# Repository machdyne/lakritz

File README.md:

# Lakritz Computer

Lakritz is an FPGA computer designed by Lone Dynamics Corporation.

This repo contains schematics, PCB layouts, pinouts, a 3D-printable case, example gateware and documentation.

Find more information on the [Lakritz product page](https://machdyne.com/product/lakritz-computer/).

## Programming Lakritz

Lakritz has a JTAG interface and ships with a [DFU bootloader](https://github.com/machdyne/tinydfu-bootloader) that allows the included flash [MMOD](https://machdyne.com/product/mmod) to be programmed over the USB-C port.

### DFU

The DFU bootloader is available for 5 seconds after power-on, issuing a DFU command during this period will stop the boot process until the DFU device is detached. If no command is received the boot process will continue and the user gateware will be loaded.

Install [dfu-util](http://dfu-util.sourceforge.net) (Debian/Ubuntu):

```
$ sudo apt install dfu-util
```

Update the user gateware on the flash MMOD:

```
$ sudo dfu-util -a 0 -D image.bit
```

Detach the DFU device and continue the boot process:

```
$ sudo dfu-util -a 0 -e
```

It is possible to update the bootloader itself using DFU but you shouldn't attempt this unless you have a JTAG programmer (or another method to program the MMOD) available, in case you need to restore the bootloader.

### JTAG

These examples assume you're using a "USB Blaster" JTAG cable, see the header pinout below. You will need to have [openFPGALoader](https://github.com/trabucayre/openFPGALoader) installed.

Program the configuration SRAM:

```
openFPGALoader -c usb-blaster image.bit
```

Program the flash MMOD:

```
openFPGALoader -f -c usb-blaster images/bootloader/tinydfu_lakritz.bit
```

## Blinky 

Building the blinky example requires [Yosys](https://github.com/YosysHQ/yosys), [nextpnr-ecp5](https://github.com/YosysHQ/nextpnr) and [Project Trellis](https://github.com/YosysHQ/prjtrellis).

Assuming they are installed, you can simply type `make` to build the gateware, which will be written to output/lakritz.bit. You can then use [openFPGALoader](https://github.com/trabucayre/openFPGALoader) or dfu-util to write the gateware to the device.

## Linux

See the [Kakao Linux](https://github.com/machdyne/kakao) repo for the latest instructions.

### Prebuilt Images

Copy the files from the `images/linux` and `images/v0/25f` directory to the root directory of a FAT-formatted MicroSD card along with the files from the `images` directory in the [Kakao Linux](https://github.com/machdyne/kakao) repo.

Lakritz ships with LiteX gateware on the user gateware section of the MMOD that is compatible with these images. After several seconds the Linux penguin should appear on the screen (HDMI) followed by a login prompt.

### Building Linux

Please follow the setup instructions in the [linux-on-litex-vexriscv](https://github.com/litex-hub/linux-on-litex-vexriscv) repo and then:

1. Build the Linux-capable gateware:

```
$ cd linux-on-litex-vexriscv
$ ./make.py --board lakritz --uart-baudrate 115200 --dcache-size 64 --icache-size 64 --dcache-ways=1 --icache-ways=1 --dtlb-size 2 --itlb-size 2 --build
```

NOTE: This may fail, if so:

```
$ cd build/lakritz/gateware
```

Edit `lakritz.ys` and add the `-abc2` option as shown below:

```
synth_ecp5  -top lakritz -abc2
```

Now run:

```
$ bash build_lakritz.sh
```

2. Write the gateware to the MMOD using USB DFU:

```
$ sudo dfu-util -a 0 -D build/lakritz/gateware/lakritz.bit
```

3. Copy the device tree binary `build/lakritz/lakritz.dtb` to a FAT-formatted MicroSD card.

4. Build the Linux kernel and root filesystem:

See the [Kakao Linux](https://github.com/machdyne/kakao?tab=readme-ov-file#optional-building-kakao-linux) repo for instructions.

5. Copy the Image and rootfs.cpio files generated in the previous step to the boot partition of the MicroSD card, in addition to the following files:

6. Copy the OpenSBI binary (included in this repo as `lakritz/images/linux/opensbi.bin`) to the MicroSD card. Alternatively, you can build this binary by following [these instructions](https://github.com/litex-hub/linux-on-litex-vexriscv#-generating-the-opensbi-binary-optional).

7. Copy `lakritz/images/linux/boot.json` to the MicroSD card.

8. Power-cycle Lakritz. After Linux has finished booting you should see a login prompt on the HDMI display.

## JTAG Header

The 3.3V JTAG header can be used to program the FPGA SRAM as well as the MMOD flash memory. It can also be used to provide power (5V) to the board.

```
2 4 6
1 3 5
```

| Pin | Signal |
| --- | ------ |
| 1 | TCK |
| 2 | TDI |
| 3 | TDO |
| 4 | TMS |
| 5 | 5V0 |
| 6 | GND |

## Resources

 * [fpga-dac audio player](https://github.com/machdyne/fpga-dac)

## Board Revisions

| Revision | Notes |
| -------- | ----- |
| V0 | Initial version |

## License

The contents of this repo are released under the [Lone Dynamics Open License](LICENSE.md) with the following exceptions:

- The KiCad design files contain parts of the [kicad-pmod](https://github.com/mithro/kicad-pmod) library which is released under the [Apache License, Version 2.0](https://www.apache.org/licenses/LICENSE-2.0.html).

- The KiCad design files may contain symbols and footprints released under other licenses; please contact us if we've failed to give proper attribution.

Note: You can use these designs for commercial purposes but we ask that instead of producing exact clones, that you either replace our trademarks and logos with your own or add your own next to ours.

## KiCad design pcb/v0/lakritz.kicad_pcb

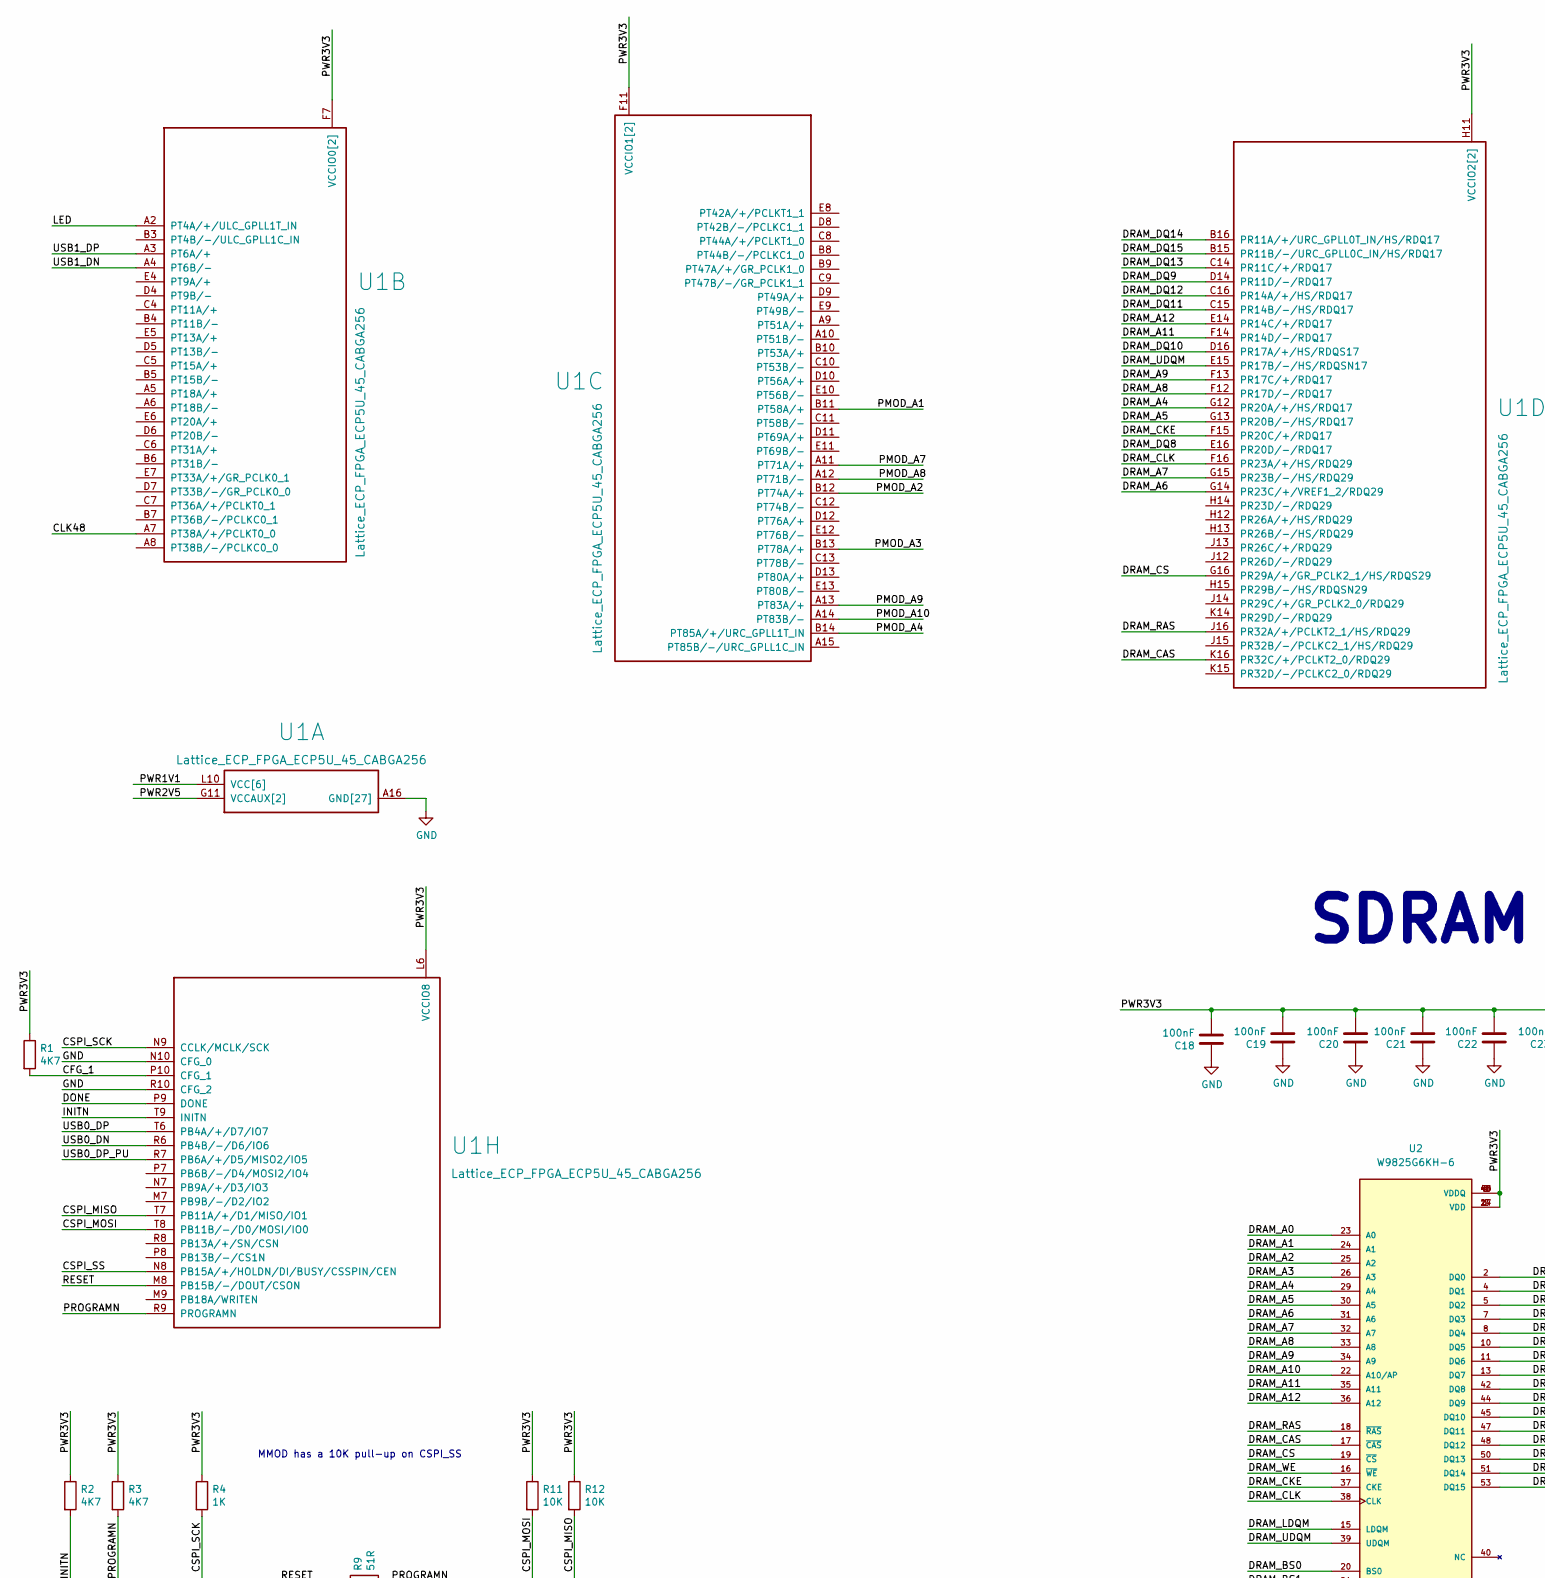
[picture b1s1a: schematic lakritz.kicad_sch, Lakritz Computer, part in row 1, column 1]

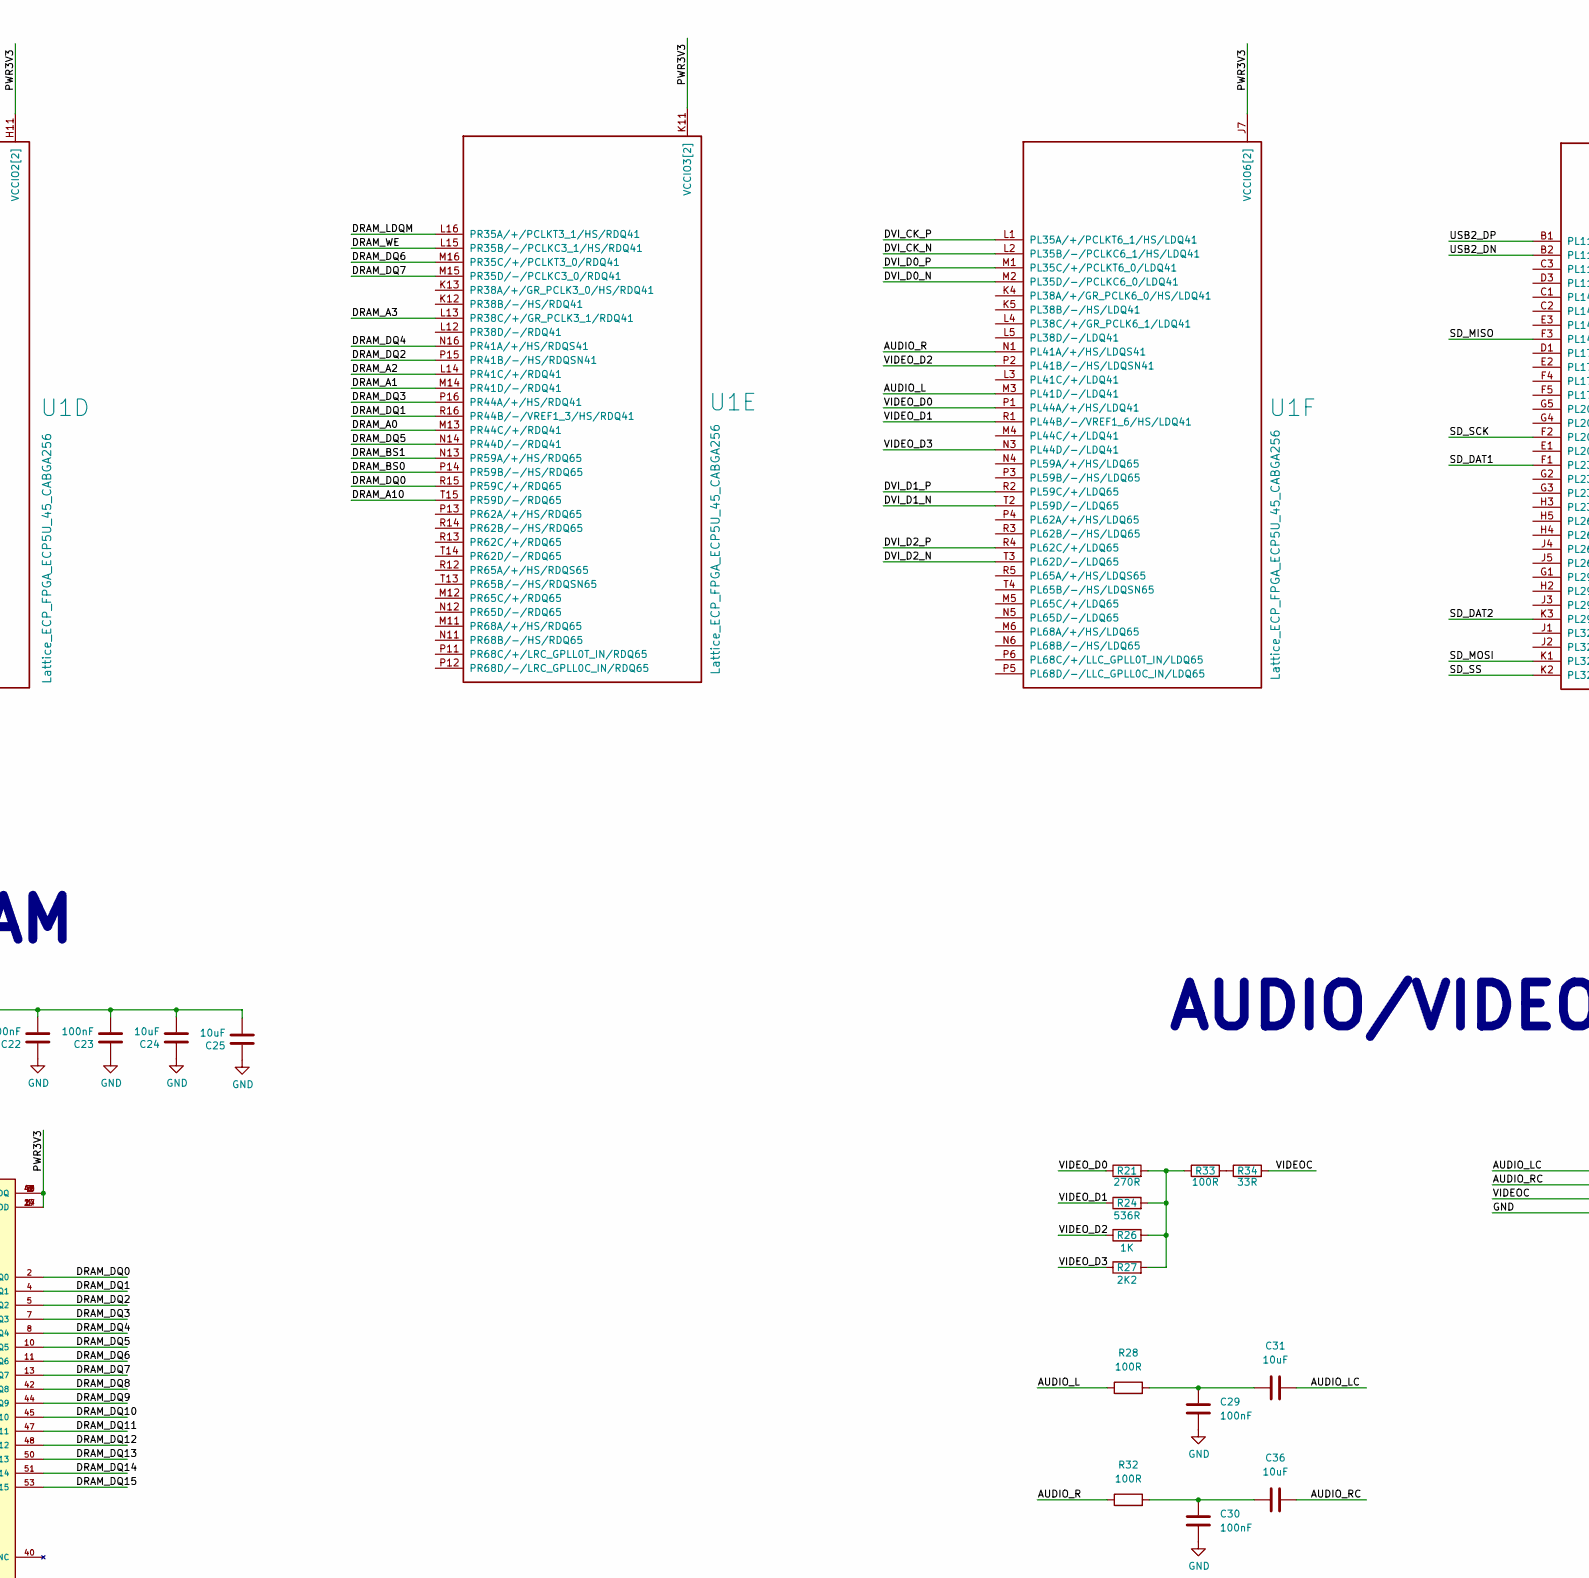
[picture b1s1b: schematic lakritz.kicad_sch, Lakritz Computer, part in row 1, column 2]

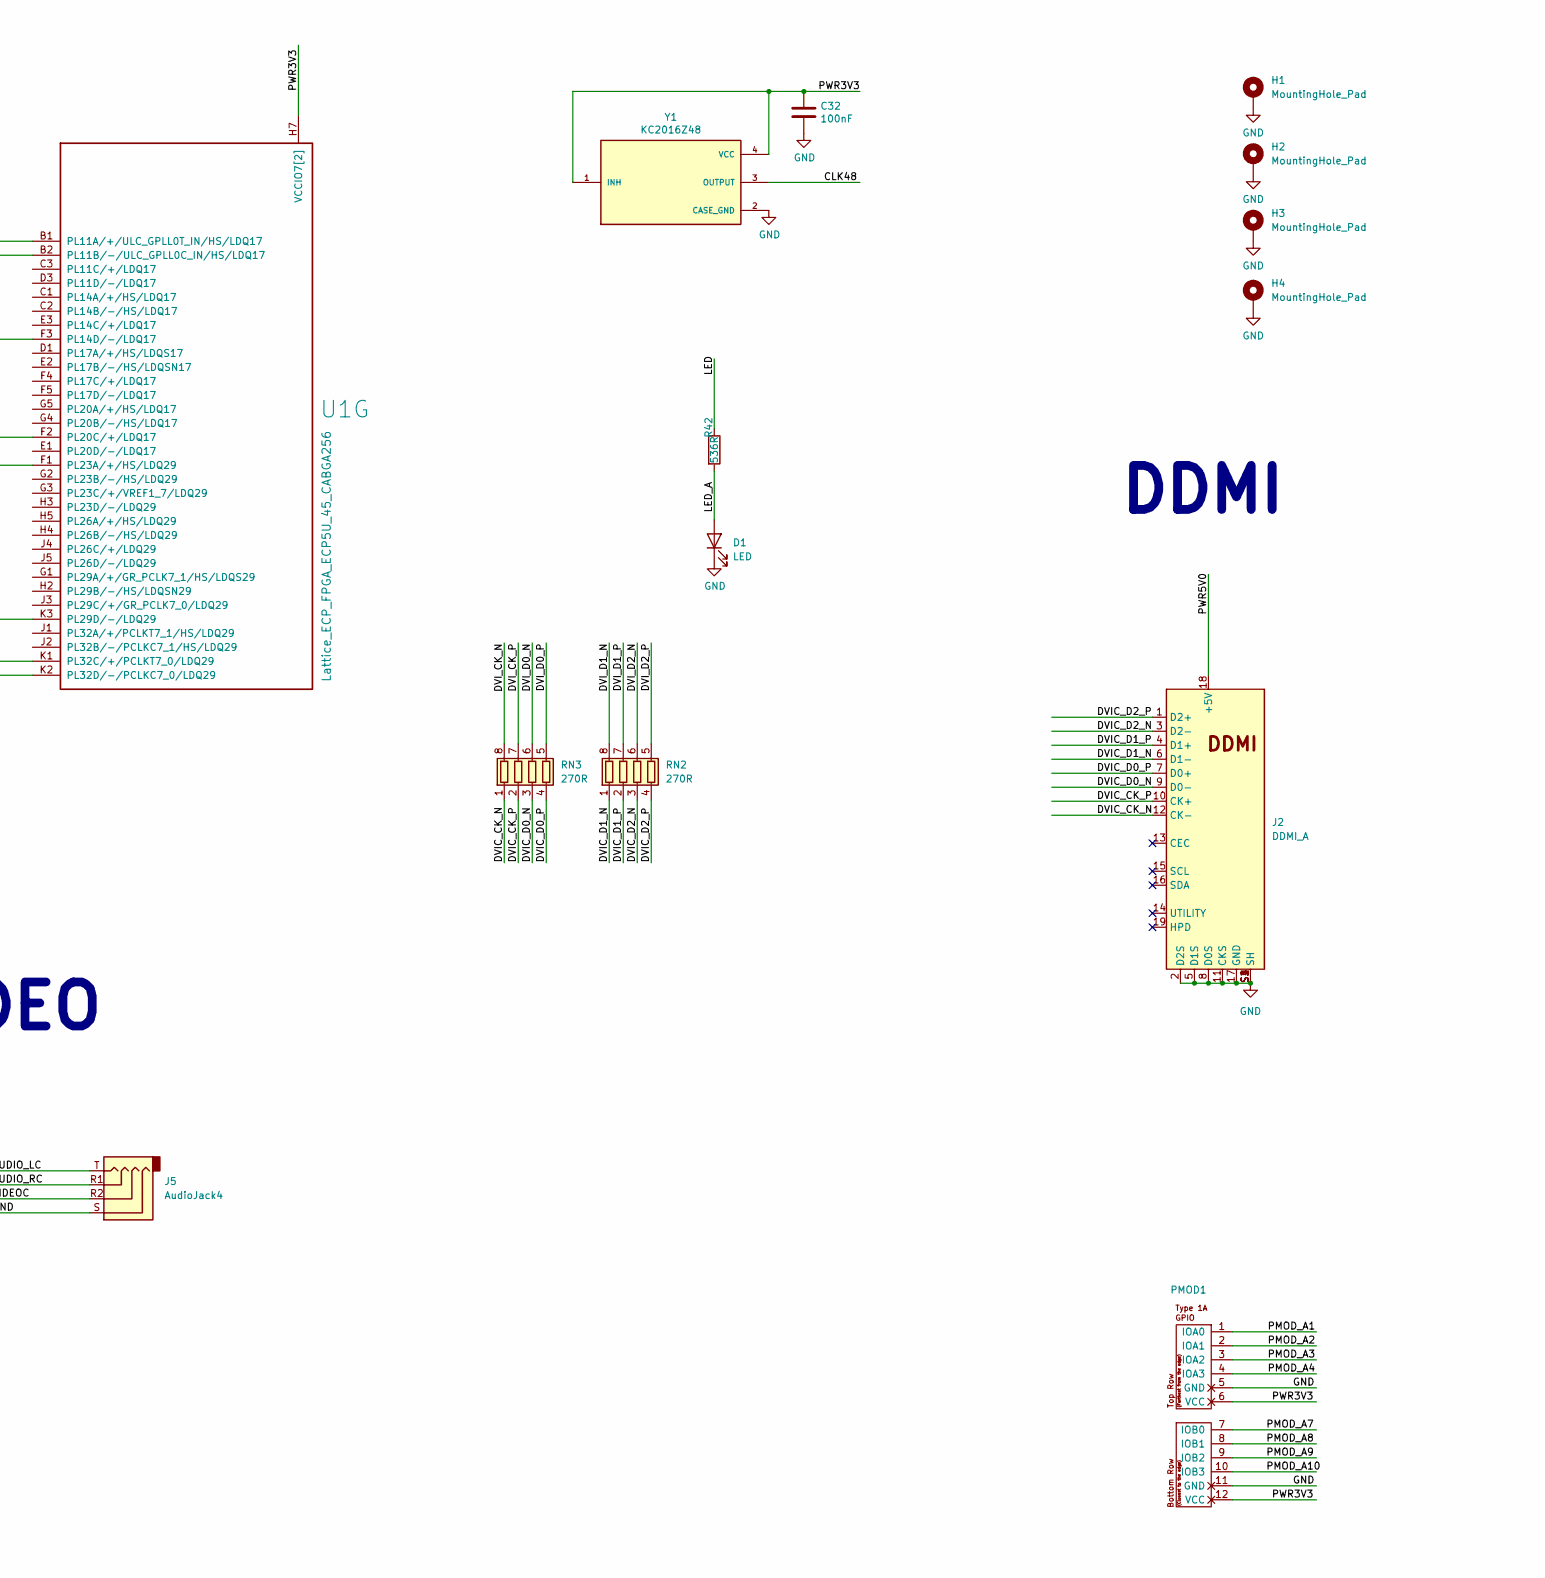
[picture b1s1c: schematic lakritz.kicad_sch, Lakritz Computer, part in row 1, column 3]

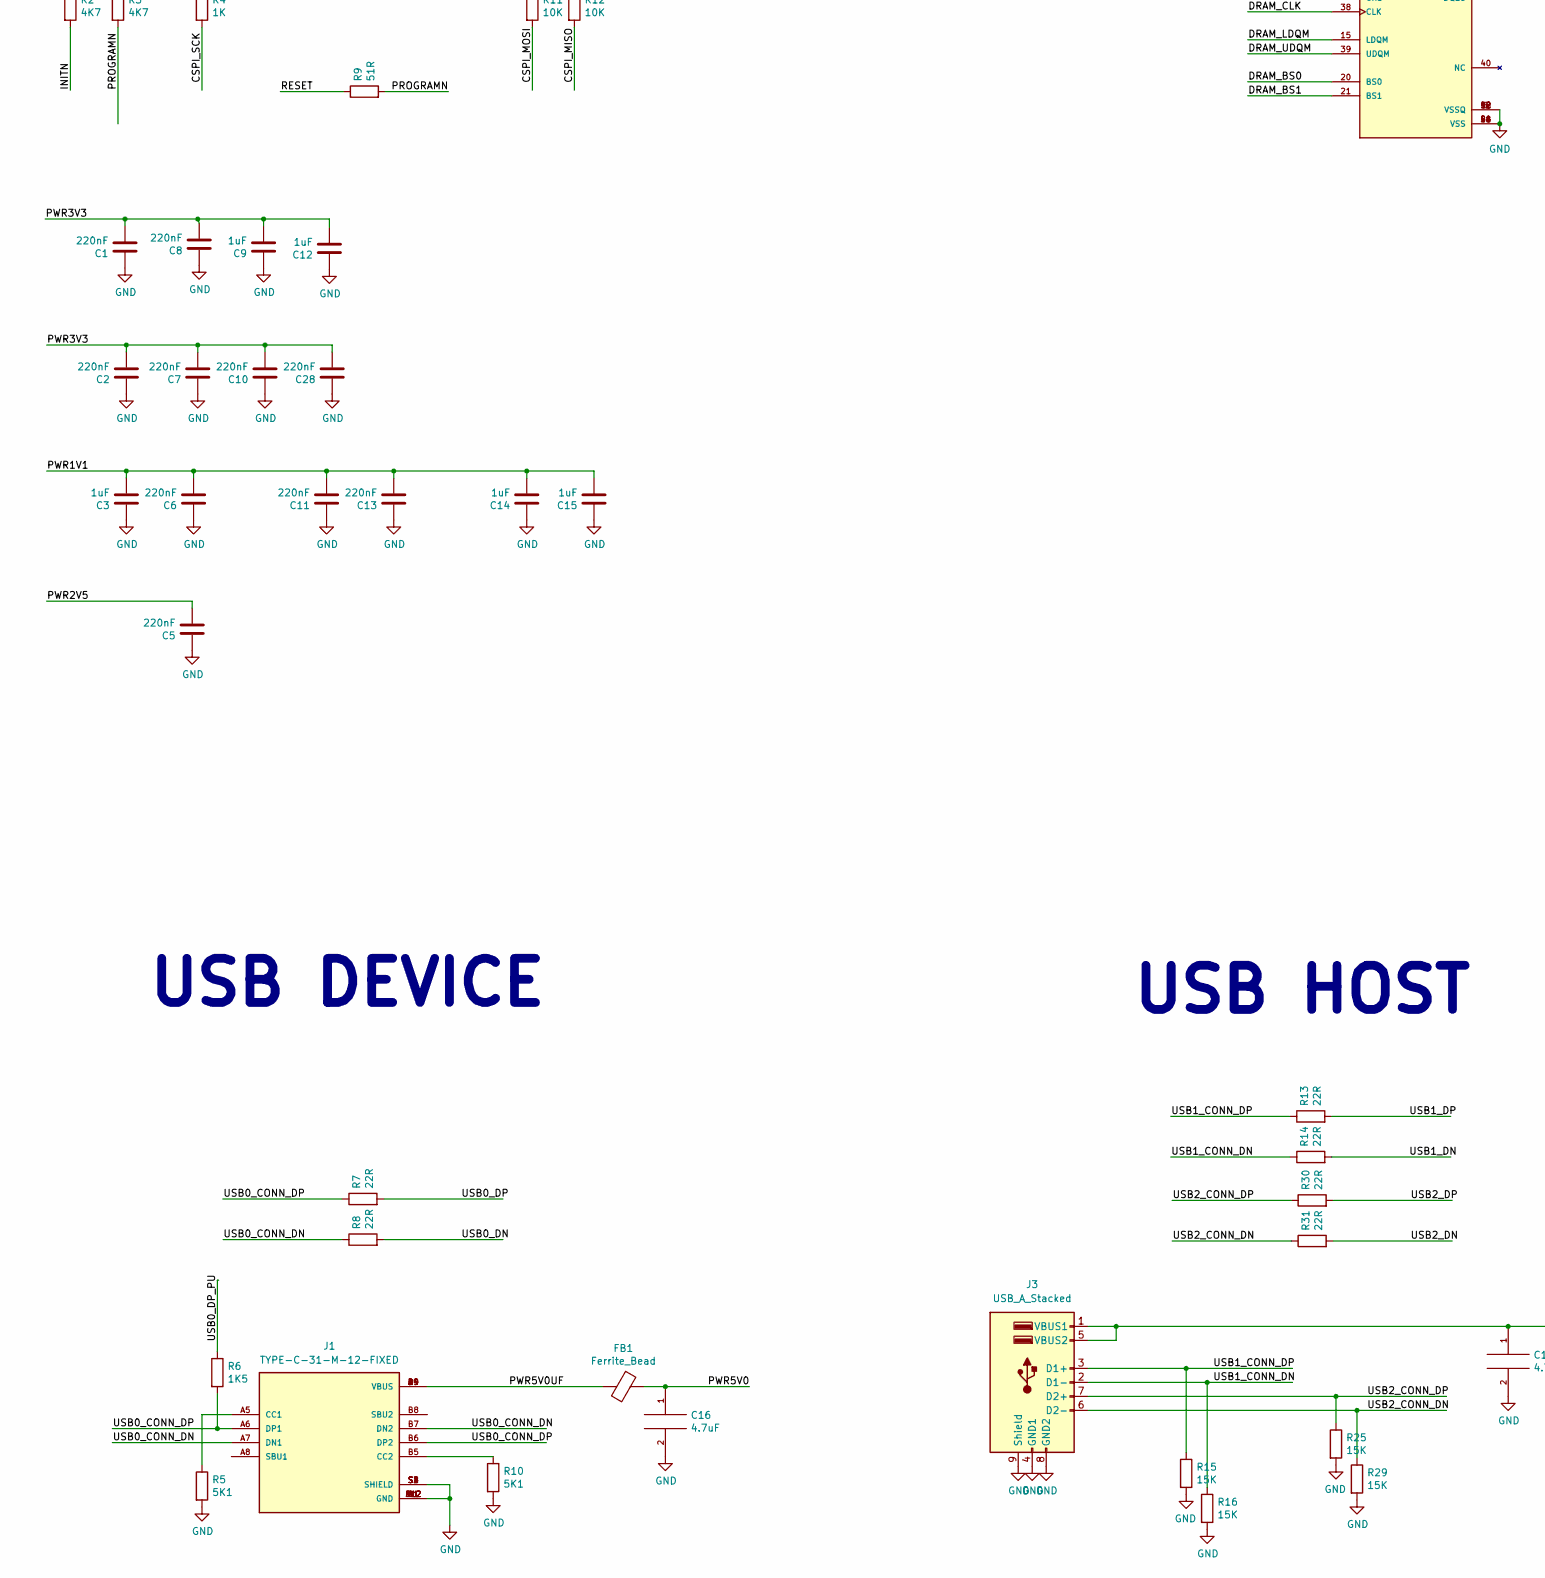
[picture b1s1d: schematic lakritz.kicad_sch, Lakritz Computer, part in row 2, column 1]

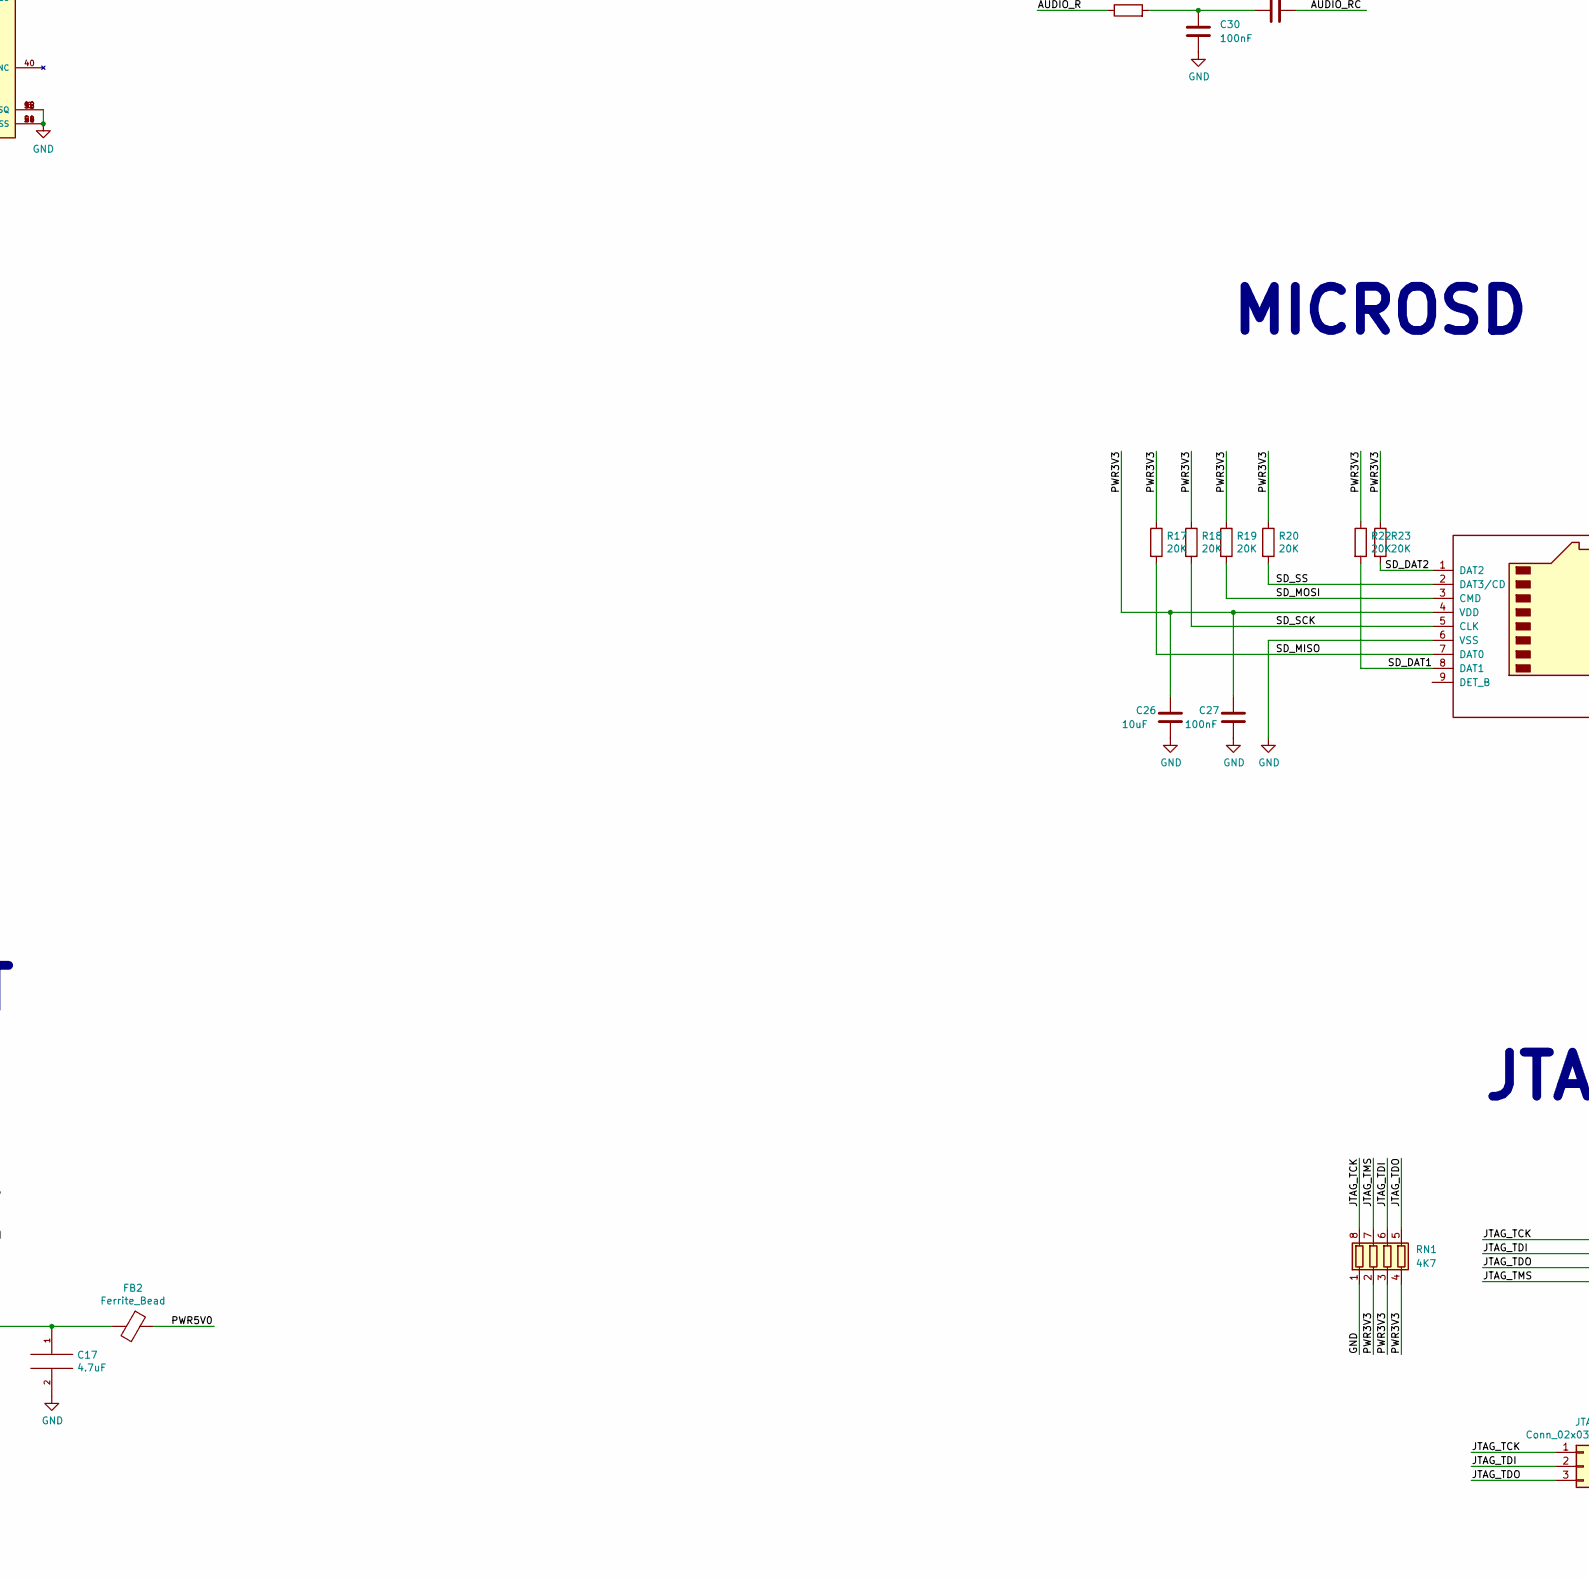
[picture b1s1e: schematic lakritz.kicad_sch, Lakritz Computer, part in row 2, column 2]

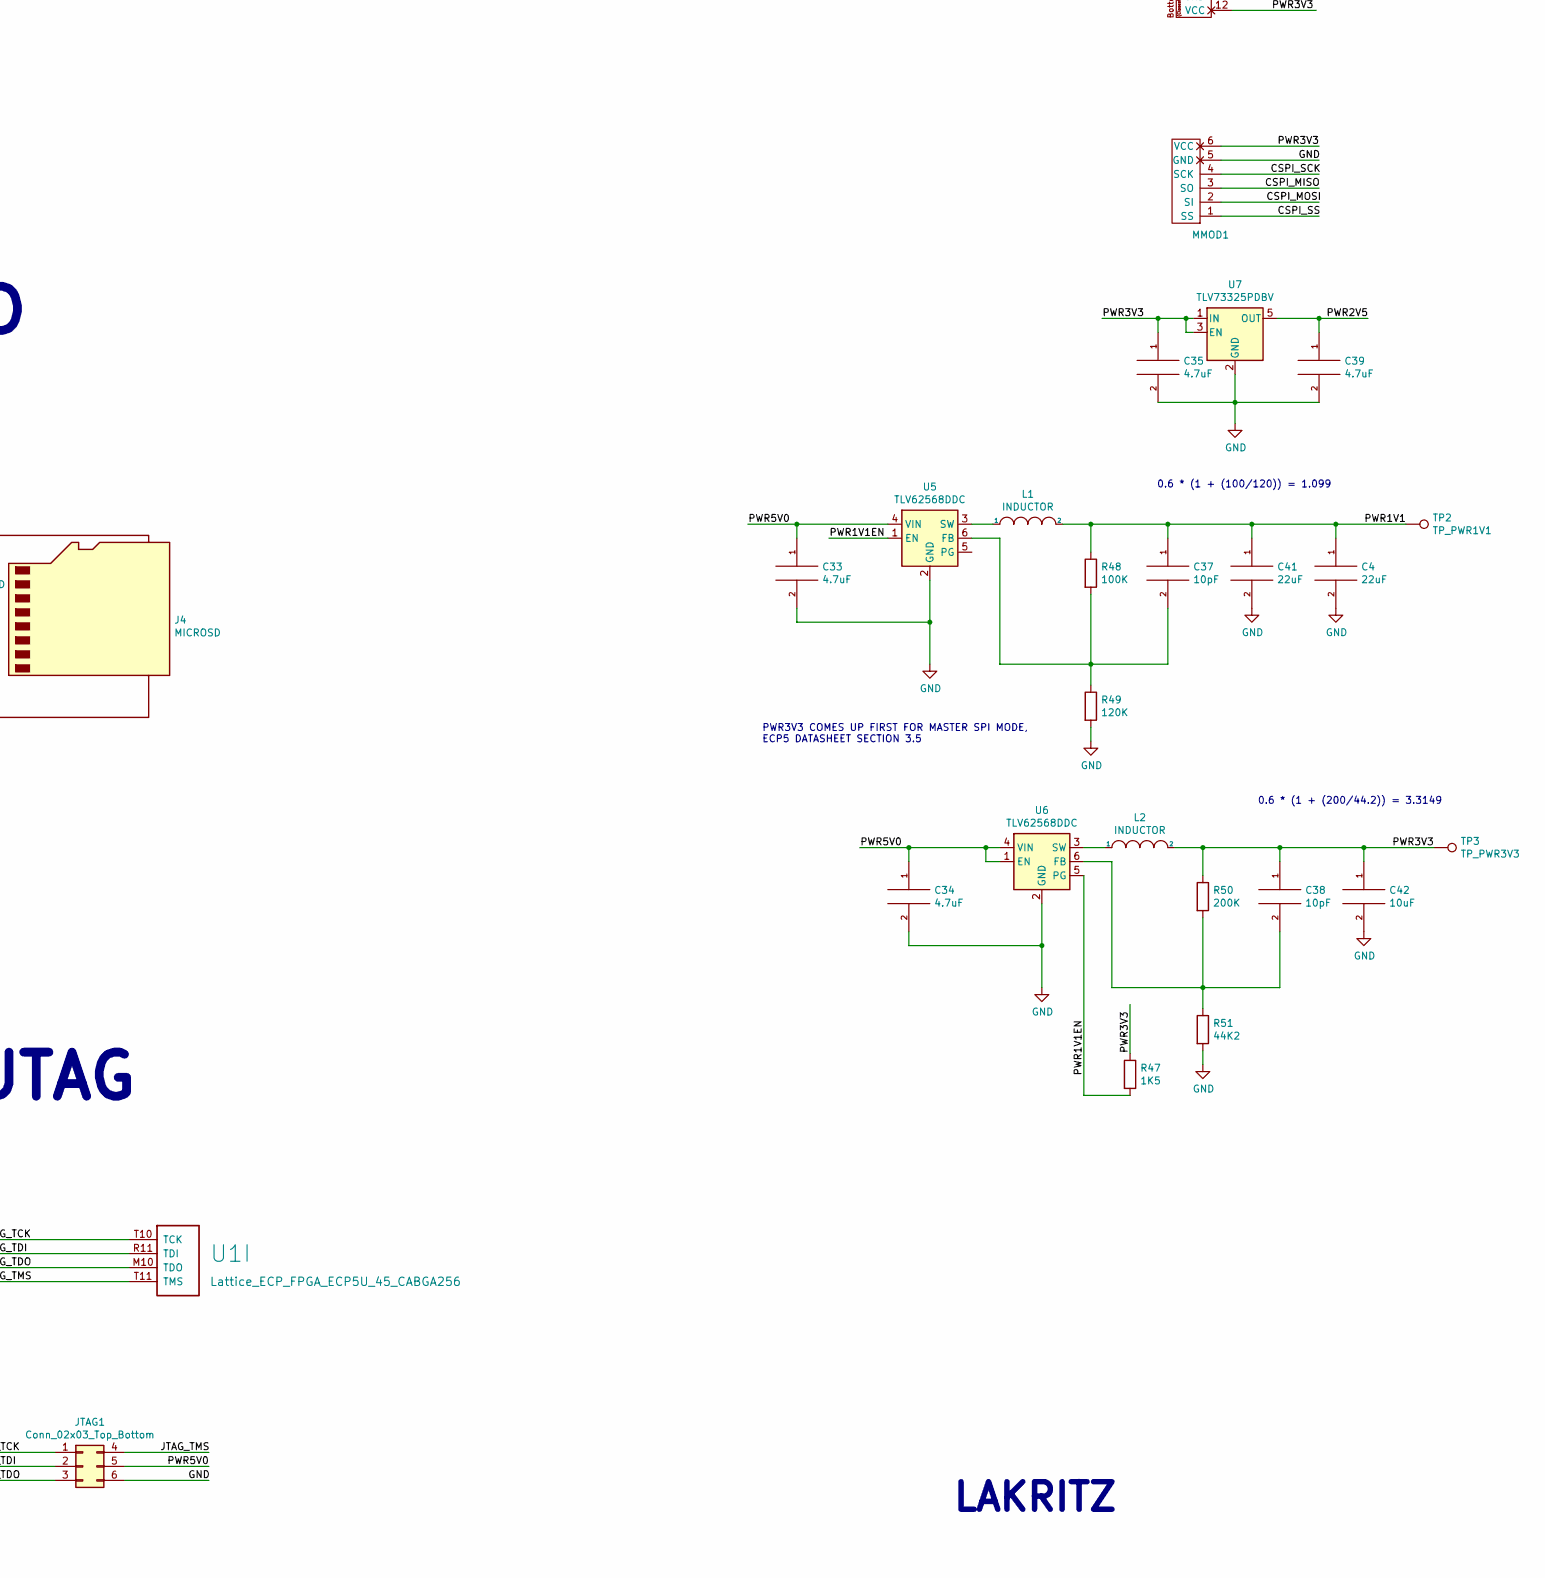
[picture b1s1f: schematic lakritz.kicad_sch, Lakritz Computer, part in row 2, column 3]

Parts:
C1, C2, C5, C6, C7, C8, C10, C11, C13, C28: 220nF; C_0603_1608Metric
C3, C9, C12, C14, C15: 1uF; C_0603_1608Metric
C4, C41: 22uF; C_0603_1608Metric
C16, C17, C33, C34, C35, C39: 4.7uF; C_0603_1608Metric
C18, C19, C20, C21, C22, C23, C27, C29, C30, C32: 100nF; C_0603_1608Metric
C24, C25, C26, C31, C36, C42: 10uF; C_0603_1608Metric
C37, C38: 10pF; C_0603_1608Metric
D1: LED; LED_0805_2012Metric
FB1, FB2: Ferrite_Bead; R_0603_1608Metric
H1, H2, H3, H4: MountingHole_Pad; MountingHole_3.2mm_M3_Pad
J1: TYPE-C-31-M-12-FIXED; USB_C_Receptacle_HRO_TYPE-C-31-M-12-BIG-PADS; PARTREV A
J2: DDMI_A; HDMI_TE_1827059-3-FIXED
J3: USB_A_Stacked; USB_A_Wuerth_61400826021_Horizontal_Stacked
J4: MICROSD; SDCARD
J5: AudioJack4; Jack_3.5mm_PJ320D_Horizontal
JTAG1: Conn_02x03_Top_Bottom; PinHeader_2x03_P2.54mm_Vertical
L1, L2: INDUCTOR; L_0805_2012Metric
MMOD1: PMOD-Device-x1-Type-2-SPI; MMOD_Host_Socket_Vertical
PMOD1: PMOD-Device-x2-Type-1A-GPIO; PMOD_2x06_HOST
R1, R2, R3: 4K7; R_0402_1005Metric
R4, R26: 1K; R_0402_1005Metric
R5, R10: 5K1; R_0603_1608Metric
R6, R47: 1K5; R_0402_1005Metric
R7, R8, R13, R14, R30, R31: 22R; R_0402_1005Metric
R9: 51R; R_0402_1005Metric
R11, R12: 10K; R_0402_1005Metric
R15, R16, R25, R29: 15K; R_0402_1005Metric
R17, R18, R19, R20, R22, R23: 20K; R_0402_1005Metric
R21: 270R; R_0402_1005Metric
R24, R42: 536R; R_0402_1005Metric
R27: 2K2; R_0402_1005Metric
R28, R32, R33: 100R; R_0402_1005Metric
R34: 33R; R_0402_1005Metric
R48: 100K; R_0603_1608Metric
R49: 120K; R_0603_1608Metric
R50: 200K; R_0603_1608Metric
R51: 44K2; R_0603_1608Metric
RN1: 4K7; R_Array_Convex_4x0402
RN2, RN3: 270R; R_Array_Convex_4x0402
TP2: TP_PWR1V1; TestPoint_THTPad_D1.0mm_Drill0.5mm
TP3: TP_PWR3V3; TestPoint_THTPad_D1.0mm_Drill0.5mm
U1: Lattice_ECP_FPGA_ECP5U_45_CABGA256; BGA-256_14.0x14.0mm_Layout16x16_P0.8mm_Ball0.45mm_Pad0.32mm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
U2: W9825G6KH-6; SOP80P1176X120-54N; PARTREV A05
U5, U6: TLV62568DDC; SOT-23-6
U7: TLV73325PDBV; SOT-23-5
Y1: KC2016Z48; OSC_KC2016Z13.5600C1KX00; PARTREV November 2020

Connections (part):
/AUDIO_L: R28.1, U1.M3 (PL41D/-/LDQ41)
/AUDIO_LC: C31.2, J5.T
/AUDIO_R: R32.1, U1.N1 (PL41A/+/HS/LDQS41)
/AUDIO_RC: C36.2, J5.R1
/CFG_1: R1.2, U1.P10 (CFG_1)
/CLK48: U1.A7 (PT38A/+/PCLKT0_0), Y1.3 (OUTPUT)
/CSPI_MISO: MMOD1.3 (SO), R12.2, U1.T7 (PB11A/+/D1/MISO/IO1)
/CSPI_MOSI: MMOD1.2 (SI), R11.2, U1.T8 (PB11B/-/D0/MOSI/IO0)
/CSPI_SCK: MMOD1.4 (SCK), R4.2, U1.N9 (CCLK/MCLK/SCK)
/CSPI_SS: MMOD1.1 (SS), U1.N8 (PB15A/+/HOLDN/DI/BUSY/CSSPIN/CEN)
/DONE: U1.P9 (DONE)
/DRAM_A0: U1.M13 (PR44C/+/RDQ41), U2.23 (A0)
/DRAM_A1: U1.M14 (PR41D/-/RDQ41), U2.24 (A1)
/DRAM_A2: U1.L14 (PR41C/+/RDQ41), U2.25 (A2)
/DRAM_A3: U1.L13 (PR38C/+/GR_PCLK3_1/RDQ41), U2.26 (A3)
/DRAM_A4: U1.G12 (PR20A/+/HS/RDQ17), U2.29 (A4)
/DRAM_A5: U1.G13 (PR20B/-/HS/RDQ17), U2.30 (A5)
/DRAM_A6: U1.G14 (PR23C/+/VREF1_2/RDQ29), U2.31 (A6)
/DRAM_A7: U1.G15 (PR23B/-/HS/RDQ29), U2.32 (A7)
/DRAM_A8: U1.F12 (PR17D/-/RDQ17), U2.33 (A8)
/DRAM_A9: U1.F13 (PR17C/+/RDQ17), U2.34 (A9)
/DRAM_A10: U1.T15 (PR59D/-/RDQ65), U2.22 (A10/AP)
/DRAM_A11: U1.F14 (PR14D/-/RDQ17), U2.35 (A11)
/DRAM_A12: U1.E14 (PR14C/+/RDQ17), U2.36 (A12)
/DRAM_BS0: U1.P14 (PR59B/-/HS/RDQ65), U2.20 (BS0)
/DRAM_BS1: U1.N13 (PR59A/+/HS/RDQ65), U2.21 (BS1)
/DRAM_CAS: U1.K16 (PR32C/+/PCLKT2_0/RDQ29), U2.17 (~CAS)
/DRAM_CKE: U1.F15 (PR20C/+/RDQ17), U2.37 (CKE)
/DRAM_CLK: U1.F16 (PR23A/+/HS/RDQ29), U2.38 (CLK)
/DRAM_CS: U1.G16 (PR29A/+/GR_PCLK2_1/HS/RDQS29), U2.19 (~CS)
/DRAM_DQ0: U1.R15 (PR59C/+/RDQ65), U2.2 (DQ0)
/DRAM_DQ1: U1.R16 (PR44B/-/VREF1_3/HS/RDQ41), U2.4 (DQ1)
/DRAM_DQ2: U1.P15 (PR41B/-/HS/RDQSN41), U2.5 (DQ2)
/DRAM_DQ3: U1.P16 (PR44A/+/HS/RDQ41), U2.7 (DQ3)
/DRAM_DQ4: U1.N16 (PR41A/+/HS/RDQS41), U2.8 (DQ4)
/DRAM_DQ5: U1.N14 (PR44D/-/RDQ41), U2.10 (DQ5)
/DRAM_DQ6: U1.M16 (PR35C/+/PCLKT3_0/RDQ41), U2.11 (DQ6)
/DRAM_DQ7: U1.M15 (PR35D/-/PCLKC3_0/RDQ41), U2.13 (DQ7)
/DRAM_DQ8: U1.E16 (PR20D/-/RDQ17), U2.42 (DQ8)
/DRAM_DQ9: U1.D14 (PR11D/-/RDQ17), U2.44 (DQ9)
/DRAM_DQ10: U1.D16 (PR17A/+/HS/RDQS17), U2.45 (DQ10)
/DRAM_DQ11: U1.C15 (PR14B/-/HS/RDQ17), U2.47 (DQ11)
/DRAM_DQ12: U1.C16 (PR14A/+/HS/RDQ17), U2.48 (DQ12)
/DRAM_DQ13: U1.C14 (PR11C/+/RDQ17), U2.50 (DQ13)
/DRAM_DQ14: U1.B16 (PR11A/+/URC_GPLL0T_IN/HS/RDQ17), U2.51 (DQ14)
/DRAM_DQ15: U1.B15 (PR11B/-/URC_GPLL0C_IN/HS/RDQ17), U2.53 (DQ15)
/DRAM_LDQM: U1.L16 (PR35A/+/PCLKT3_1/HS/RDQ41), U2.15 (LDQM)
/DRAM_RAS: U1.J16 (PR32A/+/PCLKT2_1/HS/RDQ29), U2.18 (~RAS)
/DRAM_UDQM: U1.E15 (PR17B/-/HS/RDQSN17), U2.39 (UDQM)
/DRAM_WE: U1.L15 (PR35B/-/PCLKC3_1/HS/RDQ41), U2.16 (~WE)
/DVIC_CK_N: J2.12 (CK-), RN3.1 (R1.1)
/DVIC_CK_P: J2.10 (CK+), RN3.2 (R2.1)
/DVIC_D0_N: J2.9 (D0-), RN3.3 (R3.1)
/DVIC_D0_P: J2.7 (D0+), RN3.4 (R4.1)
/DVIC_D1_N: J2.6 (D1-), RN2.1 (R1.1)
/DVIC_D1_P: J2.4 (D1+), RN2.2 (R2.1)
/DVIC_D2_N: J2.3 (D2-), RN2.3 (R3.1)
/DVIC_D2_P: J2.1 (D2+), RN2.4 (R4.1)
/DVI_CK_N: RN3.8 (R1.2), U1.L2 (PL35B/-/PCLKC6_1/HS/LDQ41)
/DVI_CK_P: RN3.7 (R2.2), U1.L1 (PL35A/+/PCLKT6_1/HS/LDQ41)
/DVI_D0_N: RN3.6 (R3.2), U1.M2 (PL35D/-/PCLKC6_0/LDQ41)
/DVI_D0_P: RN3.5 (R4.2), U1.M1 (PL35C/+/PCLKT6_0/LDQ41)
/DVI_D1_N: RN2.8 (R1.2), U1.T2 (PL59D/-/LDQ65)
/DVI_D1_P: RN2.7 (R2.2), U1.R2 (PL59C/+/LDQ65)
/DVI_D2_N: RN2.6 (R3.2), U1.T3 (PL62D/-/LDQ65)
/DVI_D2_P: RN2.5 (R4.2), U1.R4 (PL62C/+/LDQ65)
/INITN: R2.2, U1.T9 (INITN)
/JTAG_TCK: JTAG1.1, RN1.8 (R1.2), U1.T10 (TCK)
/JTAG_TDI: JTAG1.2, RN1.6 (R3.2), U1.R11 (TDI)
/JTAG_TDO: JTAG1.3, RN1.5 (R4.2), U1.M10 (TDO)
/JTAG_TMS: JTAG1.4, RN1.7 (R2.2), U1.T11 (TMS)
/LED: R42.1, U1.A2 (PT4A/+/ULC_GPLL1T_IN)
/LED_A: D1.2 (A), R42.2
/PMOD_A1: PMOD1.1 (IOA0), U1.B11 (PT58A/+)
/PMOD_A2: PMOD1.2 (IOA1), U1.B12 (PT74A/+)
/PMOD_A3: PMOD1.3 (IOA2), U1.B13 (PT78A/+)
/PMOD_A4: PMOD1.4 (IOA3), U1.B14 (PT85A/+/URC_GPLL1T_IN)
/PMOD_A7: PMOD1.7 (IOB0), U1.A11 (PT71A/+)
/PMOD_A8: PMOD1.8 (IOB1), U1.A12 (PT71B/-)
/PMOD_A9: PMOD1.9 (IOB2), U1.A13 (PT83A/+)
/PMOD_A10: PMOD1.10 (IOB3), U1.A14 (PT83B/-)
/PROGRAMN: R3.2, R9.2, U1.R9 (PROGRAMN)
/PWR1V1: C3.2, C4.1, C6.2, C11.2, C13.2, C14.2, C15.2, C37.1, C41.1, L1.2, R48.1, TP2.1, U1.G6 (VCC[6]), U1.G7 (VCC[6]), U1.G9 (VCC[6]), U1.L8 (VCC[6]), U1.L9 (VCC[6]), U1.L10 (VCC[6])
/PWR1V1EN: R47.2, U5.1 (EN), U6.5 (PG)
/PWR2V5: C5.2, C39.1, U1.G11 (VCCAUX[2]), U1.L7 (VCCAUX[2]), U7.5 (OUT)
/PWR3V3: C1.2, C2.2, C7.2, C8.2, C9.2, C10.2, C12.2, C18.2, C19.2, C20.2, C21.2, C22.2, C23.2, C24.2, C25.2, C26.1, C27.1, C28.2, C32.1, C35.1, C38.1, C42.1, J4.4 (VDD), L2.2, MMOD1.6 (VCC), PMOD1.6 (VCC), PMOD1.12 (VCC), R1.1, R2.1, R3.1, R4.1, R11.1, R12.1, R17.1, R18.1, R19.1, R20.1, R22.1, R23.1, R47.1, R50.1, RN1.2 (R2.1), RN1.3 (R3.1), RN1.4 (R4.1), TP3.1, U1.F6 (VCCIO0[2]), U1.F7 (VCCIO0[2]), U1.F10 (VCCIO1[2]), U1.F11 (VCCIO1[2]), U1.H6 (VCCIO7[2]), U1.H7 (VCCIO7[2]), U1.H11 (VCCIO2[2]), U1.J6 (VCCIO6[2]), U1.J7 (VCCIO6[2]), U1.J11 (VCCIO2[2]), U1.K11 (VCCIO3[2]), U1.L6 (VCCIO8), U1.L11 (VCCIO3[2]), U2.1 (VDD), U2.3 (VDDQ), U2.9 (VDDQ), U2.14 (VDD), U2.27 (VDD), U2.43 (VDDQ), U2.49 (VDDQ), U7.1 (IN), U7.3 (EN), Y1.1 (INH), Y1.4 (VCC)
/PWR5V0: C16.1, C33.1, C34.1, FB1.1, FB2.1, J2.18 (+5V), JTAG1.5, U5.4 (VIN), U6.1 (EN), U6.4 (VIN)
/PWR5V0UF: FB1.2, J1.A4 (VBUS), J1.A9 (VBUS), J1.B4 (VBUS), J1.B9 (VBUS)
/RESET: R9.1, U1.M8 (PB15B/-/DOUT/CSON)
/SD_DAT1: J4.8 (DAT1), R22.2, U1.F1 (PL23A/+/HS/LDQ29)
/SD_DAT2: J4.1 (DAT2), R23.2, U1.K3 (PL29D/-/LDQ29)
/SD_MISO: J4.7 (DAT0), R17.2, U1.F3 (PL14D/-/LDQ17)
/SD_MOSI: J4.3 (CMD), R19.2, U1.K1 (PL32C/+/PCLKT7_0/LDQ29)
/SD_SCK: J4.5 (CLK), R18.2, U1.F2 (PL20C/+/LDQ17)
/SD_SS: J4.2 (DAT3/CD), R20.2, U1.K2 (PL32D/-/PCLKC7_0/LDQ29)
/UART_RX: U1.J1 (PL32A/+/PCLKT7_1/HS/LDQ29)
/UART_TX: U1.J2 (PL32B/-/PCLKC7_1/HS/LDQ29)
/USB0_CONN_DN: J1.A7 (DN1), J1.B7 (DN2), R8.1
/USB0_CONN_DP: J1.A6 (DP1), J1.B6 (DP2), R6.2, R7.1
/USB0_DN: R8.2, U1.R6 (PB4B/-/D6/IO6)
/USB0_DP: R7.2, U1.T6 (PB4A/+/D7/IO7)
/USB0_DP_PU: R6.1, U1.R7 (PB6A/+/D5/MISO2/IO5)
/USB1_CONN_DN: J3.2 (D1-), R14.1, R16.1
/USB1_CONN_DP: J3.3 (D1+), R13.1, R15.1
/USB1_DN: R14.2, U1.A4 (PT6B/-)
/USB1_DP: R13.2, U1.A3 (PT6A/+)
/USB2_CONN_DN: J3.6 (D2-), R29.1, R31.1
/USB2_CONN_DP: J3.7 (D2+), R25.1, R30.1
/USB2_DN: R31.2, U1.B2 (PL11B/-/ULC_GPLL0C_IN/HS/LDQ17)
/USB2_DP: R30.2, U1.B1 (PL11A/+/ULC_GPLL0T_IN/HS/LDQ17)
/VIDEOC: J5.R2, R34.2
/VIDEO_D0: R21.1, U1.P1 (PL44A/+/HS/LDQ41)
/VIDEO_D1: R24.1, U1.R1 (PL44B/-/VREF1_6/HS/LDQ41)
/VIDEO_D2: R26.1, U1.P2 (PL41B/-/HS/LDQSN41)
/VIDEO_D3: R27.1, U1.N3 (PL44D/-/LDQ41)
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
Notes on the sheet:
LAKRITZ
PWR3V3 COMES UP FIRST FOR MASTER SPI MODE, ECP5 DATASHEET SECTION 3.5
SDRAM
0.6 * (1 + (200/44.2)) = 3.3149
MMOD has a 10K pull-up on CSPI_SS
0.6 * (1 + (100/120)) = 1.099
JTAG
USB DEVICE
AUDIO/VIDEO
DDMI
MICROSD
USB HOST

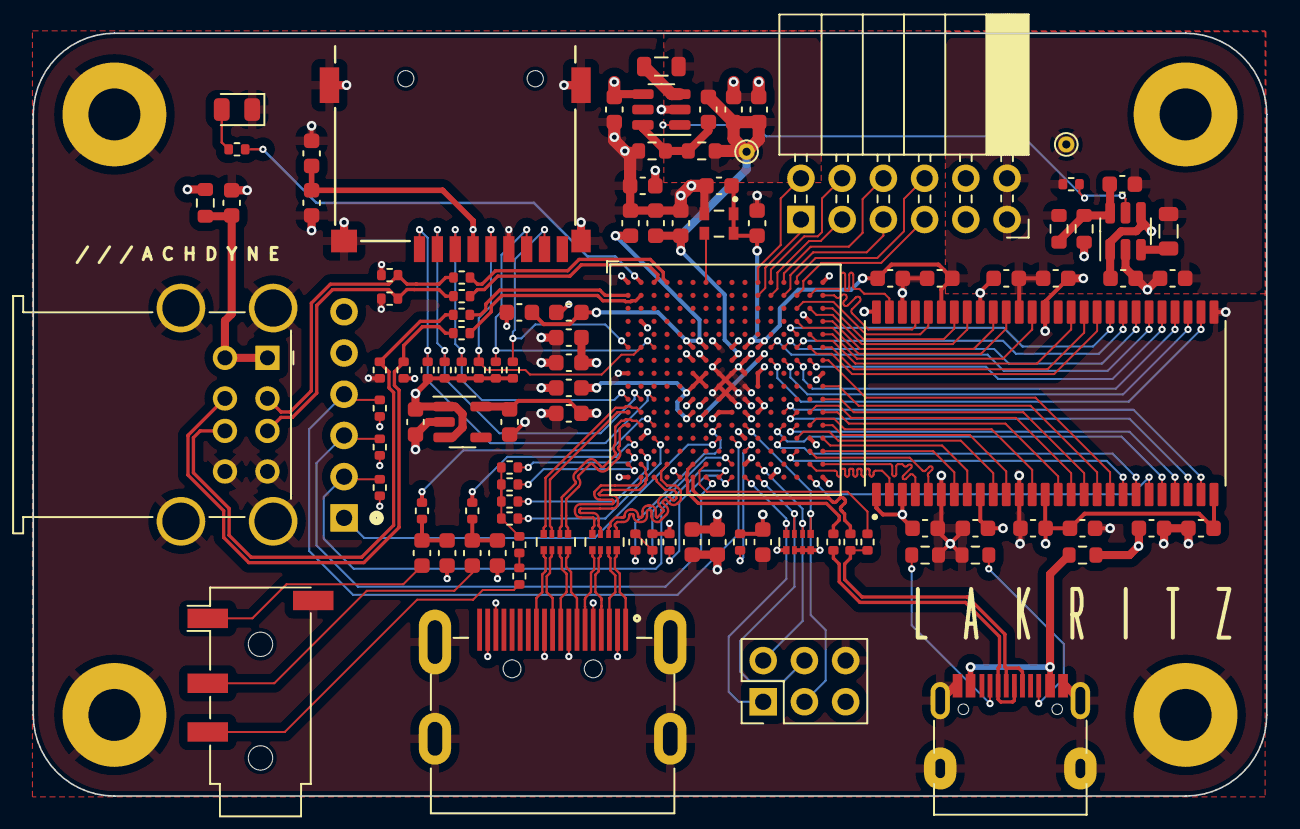
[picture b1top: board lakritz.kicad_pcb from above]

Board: 4 copper layers, 76.0 x 47.0 mm, 109 parts (0 on the bottom side), 124 nets.

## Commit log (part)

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2024-06-17 add render
2024-06-17 add schematics/pcb layout
2024-06-17 add bootloader image
2024-06-17 add case
2024-06-19 add headless bitstream
2024-06-19 add 25f bitstreams
2024-07-10 add monochrome bitstream
2024-10-05 headless ethernet via katze pmod
2025-04-30 update lpf
2025-07-24 rgb888 bitstreams

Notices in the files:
pcb/v0/lakritz.kicad_sch:
Copyright © 2024 Lone Dynamics Corporation
